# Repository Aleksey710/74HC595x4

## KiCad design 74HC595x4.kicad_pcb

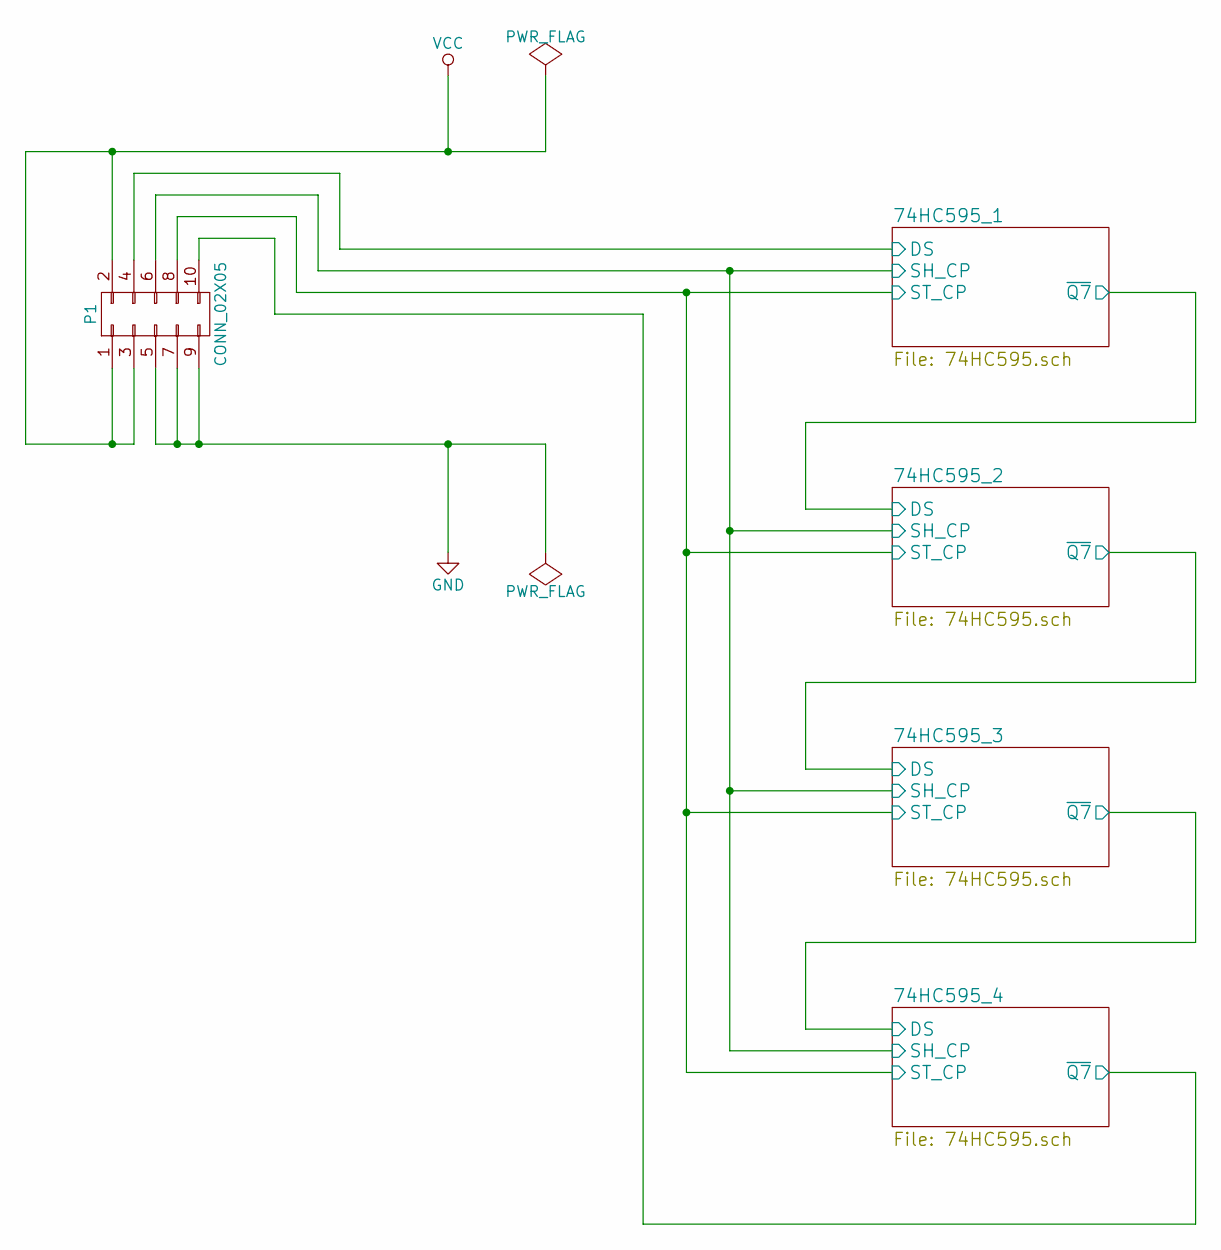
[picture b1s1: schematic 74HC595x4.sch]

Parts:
P1: CONN_02X05; IDC_Header_Straight_10pins

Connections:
/74HC595_1/DS: P1.4; also elsewhere on the board
/74HC595_1/SH_CP: P1.6; also elsewhere on the board
/74HC595_1/ST_CP: P1.8; also elsewhere on the board
/74HC595_4/~Q7: P1.10; also elsewhere on the board
GND: P1.5, P1.7, P1.9; also elsewhere on the board
VCC: P1.1, P1.2, P1.3; also elsewhere on the board

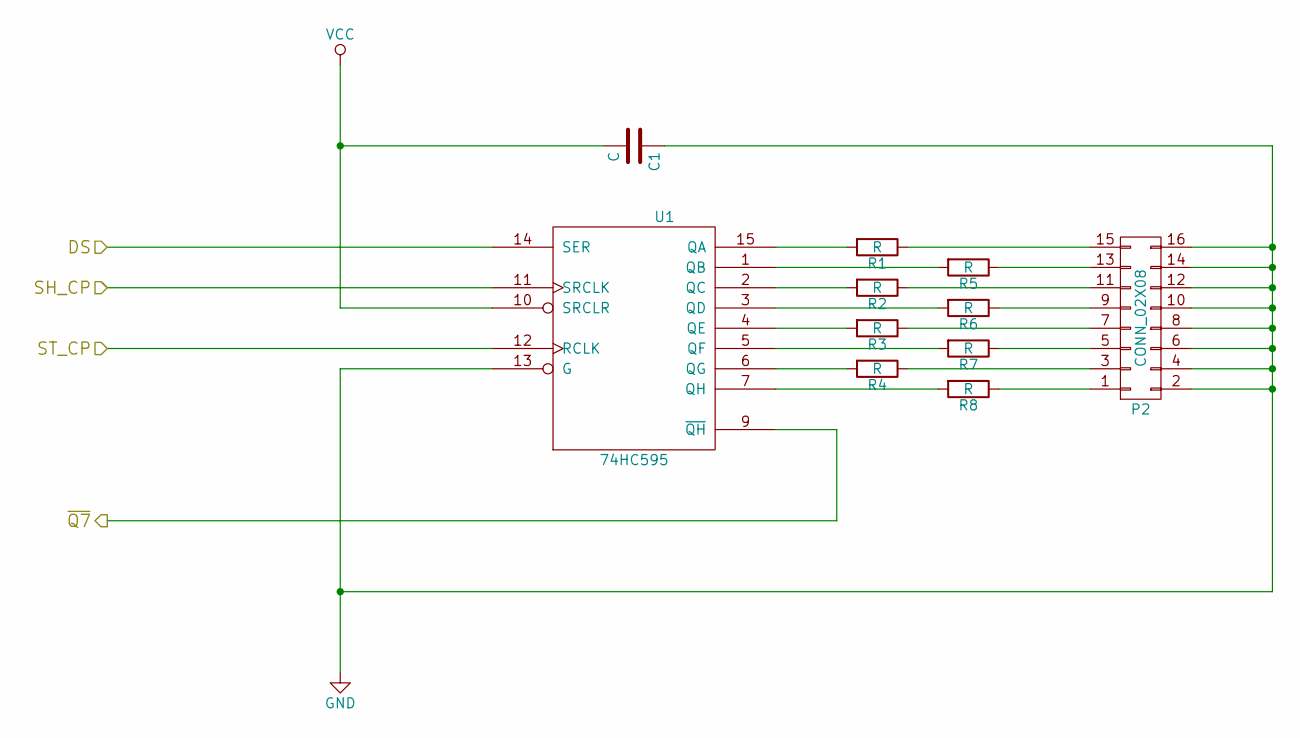
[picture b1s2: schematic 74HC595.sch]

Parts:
C1: C; C_0805_HandSoldering
P2: CONN_02X08; IDC_Header_Straight_16pins
R1, R2, R3, R4, R5, R6, R7, R8: R; R_0805_HandSoldering
U1: 74HC595; SO-16-N

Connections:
/74HC595_1/DS: U1.14 (SER); also elsewhere on the board
/74HC595_1/SH_CP: U1.11 (SRCLK); also elsewhere on the board
/74HC595_1/ST_CP: U1.12 (RCLK); also elsewhere on the board
/74HC595_2/DS: U1.9 (~QH); also elsewhere on the board
GND: C1.1, P2.2, P2.4, P2.6, P2.8, P2.10, P2.12, P2.14, P2.16, U1.8 (GND), U1.13 (G); also elsewhere on the board
unnamed: P2.1, R8.1
unnamed: P2.3, R4.1
unnamed: P2.5, R7.1
unnamed: P2.7, R3.1
unnamed: P2.9, R6.1
unnamed: P2.11, R2.1
unnamed: P2.13, R5.1
unnamed: P2.15, R1.1
unnamed: R1.2, U1.15 (QA)
unnamed: R2.2, U1.2 (QC)
unnamed: R3.2, U1.4 (QE)
unnamed: R4.2, U1.6 (QG)
unnamed: R5.2, U1.1 (QB)
unnamed: R6.2, U1.3 (QD)
unnamed: R7.2, U1.5 (QF)
unnamed: R8.2, U1.7 (QH)
VCC: C1.2, U1.10 (SRCLR), U1.16 (VCC); also elsewhere on the board

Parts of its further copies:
C2, C3, C4: C; C_0805_HandSoldering
P3, P4, P5: CONN_02X08; IDC_Header_Straight_16pins
R9, R10, R11, R12, R13, R14, R15, R16, R17, R18, R19, R20, R21, R22, R23, R24, R25, R26, R27, R28, R29, R30, R31, R32: R; R_0805_HandSoldering
U2, U3, U4: 74HC595; SO-16-N

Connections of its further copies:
/74HC595_1/SH_CP: U2.11 (SRCLK), U3.11 (SRCLK), U4.11 (SRCLK); also elsewhere on the board
/74HC595_1/ST_CP: U2.12 (RCLK), U3.12 (RCLK), U4.12 (RCLK); also elsewhere on the board
/74HC595_2/DS: U2.14 (SER); also elsewhere on the board
/74HC595_3/DS: U2.9 (~QH), U3.14 (SER)
/74HC595_4/DS: U3.9 (~QH), U4.14 (SER)
/74HC595_4/~Q7: U4.9 (~QH); also elsewhere on the board
GND: C2.1, C3.1, C4.1, P3.2, P3.4, P3.6, P3.8, P3.10, P3.12, P3.14, P3.16, P4.2, P4.4, P4.6, P4.8, P4.10, P4.12, P4.14, P4.16, P5.2, P5.4, P5.6, P5.8, P5.10, P5.12, P5.14, P5.16, U2.8 (GND), U2.13 (G), U3.8 (GND), U3.13 (G), U4.8 (GND), U4.13 (G); also elsewhere on the board
unnamed: P3.1, R16.1
unnamed: P3.3, R12.1
unnamed: P3.5, R15.1
unnamed: P3.7, R11.1
unnamed: P3.9, R14.1
unnamed: P3.11, R10.1
unnamed: P3.13, R13.1
unnamed: P3.15, R9.1
unnamed: P4.1, R24.1
unnamed: P4.3, R20.1
unnamed: P4.5, R23.1
unnamed: P4.7, R19.1
unnamed: P4.9, R22.1
unnamed: P4.11, R18.1
unnamed: P4.13, R21.1
unnamed: P4.15, R17.1
unnamed: P5.1, R32.1
unnamed: P5.3, R28.1
unnamed: P5.5, R31.1
unnamed: P5.7, R27.1
unnamed: P5.9, R30.1
unnamed: P5.11, R26.1
unnamed: P5.13, R29.1
unnamed: P5.15, R25.1
unnamed: R9.2, U2.15 (QA)
unnamed: R10.2, U2.2 (QC)
unnamed: R11.2, U2.4 (QE)
unnamed: R12.2, U2.6 (QG)
unnamed: R13.2, U2.1 (QB)
unnamed: R14.2, U2.3 (QD)
unnamed: R15.2, U2.5 (QF)
unnamed: R16.2, U2.7 (QH)
unnamed: R17.2, U3.15 (QA)
unnamed: R18.2, U3.2 (QC)
unnamed: R19.2, U3.4 (QE)
unnamed: R20.2, U3.6 (QG)
unnamed: R21.2, U3.1 (QB)
unnamed: R22.2, U3.3 (QD)
unnamed: R23.2, U3.5 (QF)
unnamed: R24.2, U3.7 (QH)
unnamed: R25.2, U4.15 (QA)
unnamed: R26.2, U4.2 (QC)
unnamed: R27.2, U4.4 (QE)
unnamed: R28.2, U4.6 (QG)
unnamed: R29.2, U4.1 (QB)
unnamed: R30.2, U4.3 (QD)
unnamed: R31.2, U4.5 (QF)
unnamed: R32.2, U4.7 (QH)
VCC: C2.2, C3.2, C4.2, U2.10 (SRCLR), U2.16 (VCC), U3.10 (SRCLR), U3.16 (VCC), U4.10 (SRCLR), U4.16 (VCC); also elsewhere on the board

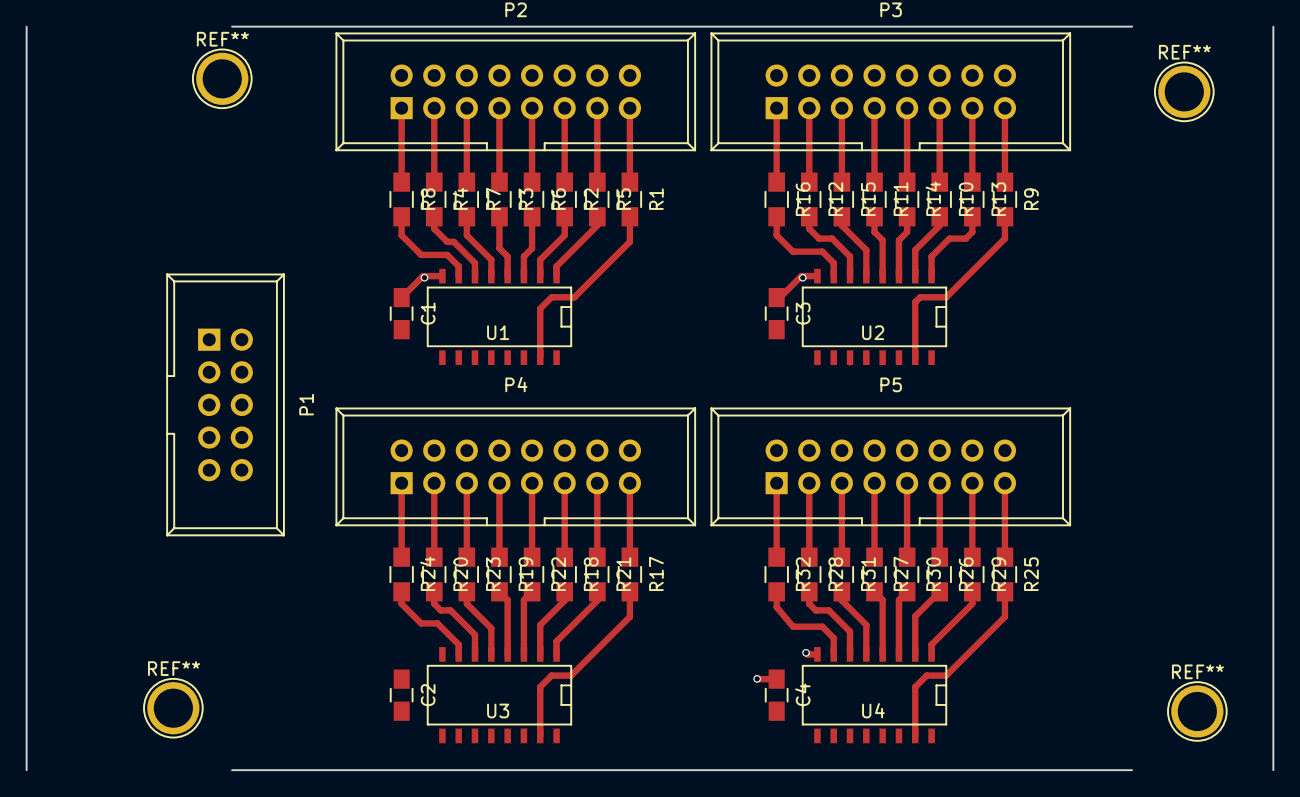
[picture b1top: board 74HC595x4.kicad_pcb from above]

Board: 2 copper layers, 97.1 x 57.9 mm, 45 parts (0 on the bottom side), 73 nets.

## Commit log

2016-09-21 Плата недоразведена
2016-10-29 расставлено по сетке, исправлены ошибки
2016-10-31 пред готовность. толстые питающие метрические размеры
2016-10-31 мелкие доделки переразвод
2016-11-28 изменен входной разъем
